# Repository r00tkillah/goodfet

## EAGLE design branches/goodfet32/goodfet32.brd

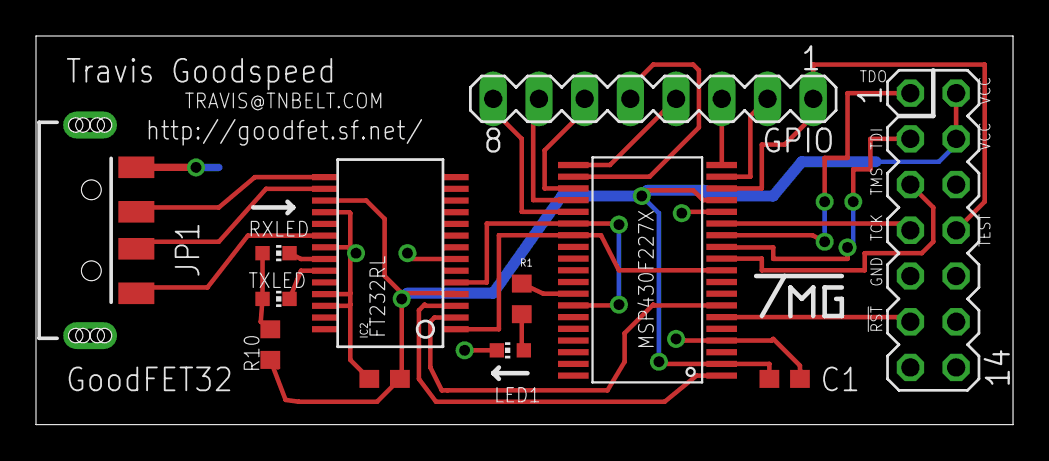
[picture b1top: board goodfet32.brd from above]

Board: 2 copper layers, 54.3 x 21.6 mm, 12 parts (0 on the bottom side), 27 nets.

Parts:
C1, C4: 0.1µF; C0603
GPIO: MA08-1
IC1: F22X4---DA38; DA38
IC2: FT232RL-BASICSSOP; SSOP28DB
JP1: USBA-SMD-MALE; USB-A-SMT-MALE
JTAG: MA07-2
LED1: CHIP-LED0603
R1: 330; R0603
R10: 300; R0603
RXLED: CHIP-LED0603
TXLED: CHIP-LED0603

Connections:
DTR: IC1.7, IC2.2
GND: C1.1, C4.1, IC1.4, IC1.15, IC2.7, IC2.18, IC2.21, IC2.25, IC2.26, JP1.GND1, JTAG.9, LED1.C
unnamed: IC2.15, JP1.D+1
unnamed: IC2.16, JP1.D-1
unnamed: IC2.22, RXLED.C
unnamed: IC2.23, TXLED.C
unnamed: R10.1, RXLED.A, TXLED.A
unnamed: IC1.31, R1.2
unnamed: LED1.A, R1.1
P4.1: GPIO.2, IC1.18
P4.2: GPIO.3, IC1.19
P4.3: GPIO.4, IC1.20
P4.4: GPIO.5, IC1.21
P4.5: GPIO.6, IC1.22
P4.6: GPIO.7, IC1.23
P4.7: GPIO.8, IC1.24
RST: IC1.6, JTAG.11
RTS: IC1.1, IC2.3
RXD: IC1.10, IC1.26, IC2.1
TCK: IC1.14, JTAG.7
TDI: IC1.12, JTAG.3
TDO: IC1.13, JTAG.1
TEST: GPIO.1, IC1.17, JTAG.8
TMS: IC1.11, JTAG.5
TXD: IC1.25, IC1.32, IC2.5
VCC: C1.2, C4.2, IC1.2, IC1.16, IC2.4, IC2.17, JTAG.2, JTAG.4, R10.2
VCC5V: IC2.20, JP1.VBUS1

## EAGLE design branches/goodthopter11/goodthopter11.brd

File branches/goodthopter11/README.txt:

If you like this project, the following will humbly accept beer
donations:

Project Lead:
 Andrew Righter

Design and Schematic:
 Andrew Righter
 Travis Goodspeed

Board and Routing:
 Ryan Barnes

CAN Hacking Inspired By:
-Late night drinking in the Midwest with atlas and cutaway

This is the sexy GoodFET CAN Adapter, its purpose is to build an
adapter that can handle CAN connection from an automobile or ECU into
a laptop leveraging the maturing GoodFET firmware and project.

Future releases may include radio (RF) hardware appliable to vehicle
applications and other fun things, if you have any questions/comments:

Andrew Righter <andrew@215LAB.com>

bugs/development:
goodfet-devel@lists.sourceforge.net

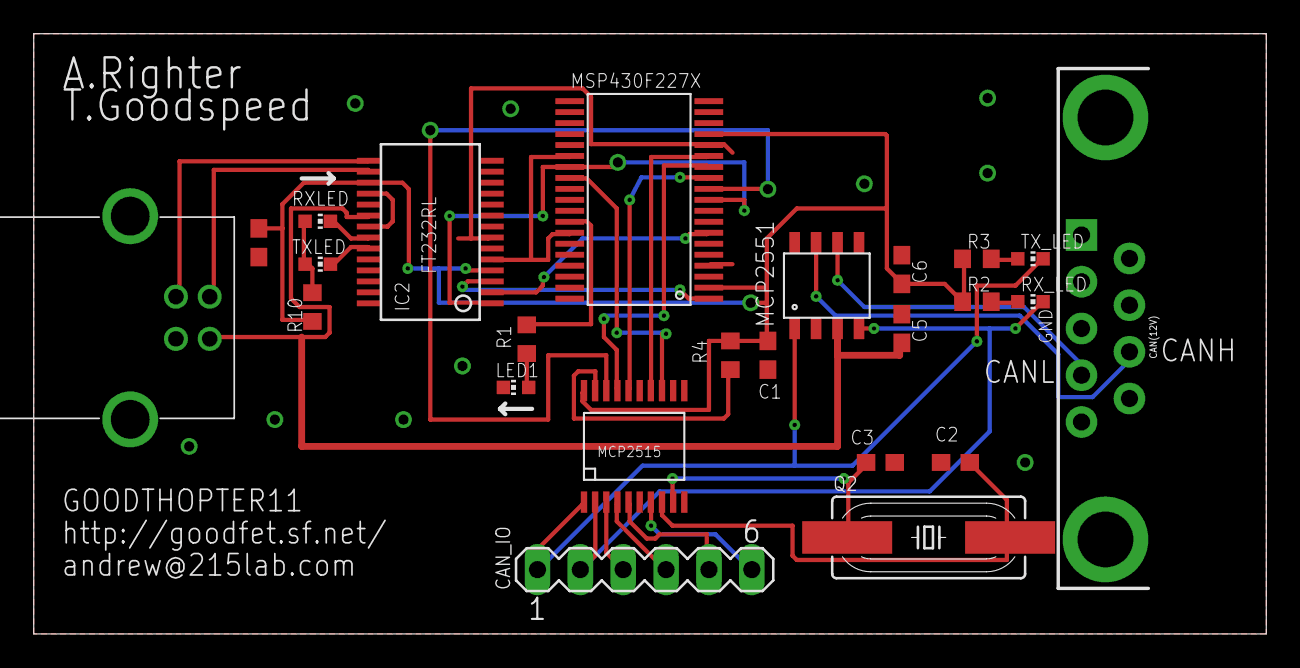
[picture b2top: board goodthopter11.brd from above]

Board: 2 copper layers, 73.0 x 35.6 mm, 24 parts (0 on the bottom side), 32 nets.

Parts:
292304-2: MINI-USB_4P-292304-2; 85-32004-10X
C1, C4: 0.1µF; C0603
C2, C3: 15pF; C0603
C5, C6: 0.1uF; C0603
CAN(12V): DB9_MALE
CAN_IO: MA06-1
IC1: F22X4---DA38; DA38
IC2: FT232RL-BASICSSOP; SSOP28DB
LED1: CHIP-LED0603
Q2: 20MHz; HC49UP
R1, R2, R3, R10: 330; R0603
R4: 10k; R0603
RXLED: CHIP-LED0603
RX_LED: CHIP-LED0603
TXLED: CHIP-LED0603
TX_LED: CHIP-LED0603
U$1: MCP2515; TSSOP20
U$2: MCP2551; SOIC-8

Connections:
!CS: IC1.11, U$1.18
!INT: IC1.27, U$1.13
!TX0RTS: CAN_IO.4, U$1.4
!TX1RTS: CAN_IO.5, U$1.5
!TX2RTS: CAN_IO.6, U$1.7
CANH: CAN(12V).7, U$2.CANH
CANL: CAN(12V).2, U$2.CANL
CLKOUT: CAN_IO.3, U$1.3
DTR: IC1.7, IC2.2
GND: 292304-2.4, C1.1, C2.1, C3.1, C4.1, C5.1, C6.1, CAN(12V).3, IC1.4, IC1.15, IC2.7, IC2.18, IC2.21, IC2.25, IC2.26, LED1.C, U$1.10, U$2.RS, U$2.VSS
MISO: IC1.13, U$1.17
MOSI: IC1.12, U$1.16
unnamed: R2.2, RX_LED.A
unnamed: R3.2, TX_LED.A
unnamed: R4.2, U$1.19
unnamed: IC2.22, RXLED.C
unnamed: IC2.23, TXLED.C
unnamed: R10.1, RXLED.A, TXLED.A
unnamed: IC1.31, R1.2
unnamed: LED1.A, R1.1
OSC1: C3.2, Q2.1, U$1.9
OSC2: C2.2, Q2.2, U$1.8
RTS: IC1.1, IC2.3
RXCAN: CAN_IO.2, RX_LED.C, U$1.2, U$2.RXD
RXD: IC1.10, IC1.26, IC2.1
SCK: IC1.14, U$1.14
TXCAN: CAN_IO.1, TX_LED.C, U$1.1, U$2.TXD
TXD: IC1.25, IC1.32, IC2.5
USBDM: 292304-2.2, IC2.16
USBDP: 292304-2.3, IC2.15
VCC: C1.2, C4.2, C6.2, IC1.2, IC1.16, IC2.4, IC2.17, R2.1, R3.1, R4.1, R10.2, U$1.20
VCC5V: 292304-2.1, C5.2, IC2.20, U$2.VDD

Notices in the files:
parts and their libraries:
SparkFun-Connectors: Licensing: CC v3.0 Share-Alike You are welcome to use this library for commercial purposes.
